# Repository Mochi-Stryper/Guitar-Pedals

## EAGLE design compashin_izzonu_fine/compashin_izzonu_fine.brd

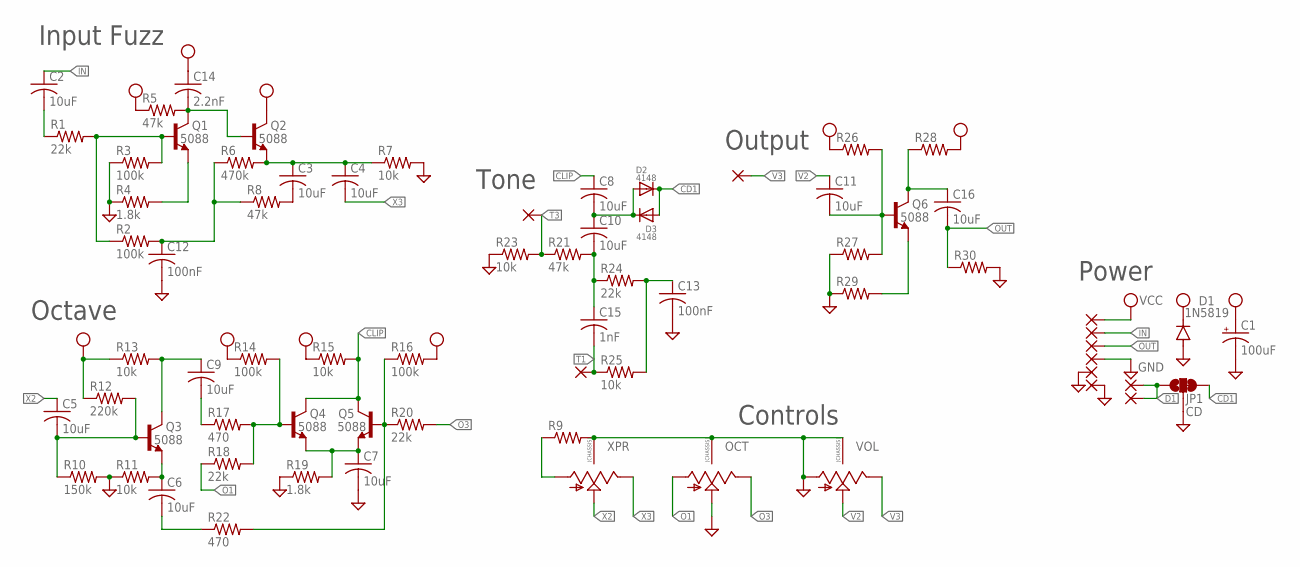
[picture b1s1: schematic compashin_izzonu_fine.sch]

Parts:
C1: 100uF; CPOL-RADIAL-2.5MM-6.5MM
C2, C3, C4, C5, C6, C7, C8, C9, C10, C11, C16: 10uF; C0805
C12, C13: 100nF; C0402
C14: 2.2nF; C0402
C15: 1nF; C0402
D1: 1N5819; SOD123
D2, D3: 4148; SOD-123
JP1: CD; SMT-JUMPER_3_1-NC_TRACE_SILK
OCT: 9MM_SNAP-IN_POT_CHASSIS; 9MM_SNAP-IN_POT
PAD1, PAD2, PAD3, PAD4, PAD5, PAD6, PAD7, PAD8: 1,6/0,8
Q1, Q2, Q3, Q4, Q5, Q6: 5088; SOT23-BEC
R1, R18, R20, R24: 22k; R0402
R2, R3, R14, R16: 100k; R0402
R4, R19: 1.8k; R0402
R5, R8, R21: 47k; R0402
R6: 470k; R0402
R7, R11, R13, R15, R23, R25: 10k; R0402
R9, R26, R27, R28, R29, R30: R-US_R0402; R0402
R10: 150k; R0402
R12: 220k; R0402
R17, R22: 470; R0402
T1, T2, T3: 1,6/0,8
VOL: 9MM_SNAP-IN_POT_CHASSIS; 9MM_SNAP-IN_POT
XPR: 9MM_SNAP-IN_POT_CHASSIS; 9MM_SNAP-IN_POT

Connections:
CD1: D2.C, D3.A, JP1.3
CLIP: C8.1, Q4.C, Q5.C, R15.2
D1: JP1.1, PAD7.1, PAD8.1
GND: C1.2 (-), C7.2, C12.2, C13.2, D1.A, JP1.2, OCT.2 (S), OCT.CHASSIS1, OCT.CHASSIS2, PAD4.1, PAD5.1, PAD6.1, R3.1, R4.1, R7.2, R9.2, R10.2, R11.1, R19.1, R23.1, R27.1, R29.1, R30.2, VOL.1 (A), VOL.CHASSIS1, VOL.CHASSIS2, XPR.CHASSIS1, XPR.CHASSIS2
IN: C2.1, PAD2.1
unnamed: Q1.B, R1.2, R2.1, R3.2
unnamed: C2.2, R1.1
unnamed: C14.2, Q1.C, Q2.B, R5.2
unnamed: Q1.E, R4.2
unnamed: C12.1, R2.2, R6.1, R8.1
unnamed: C3.1, C4.1, Q2.E, R6.2, R7.1
unnamed: C3.2, R8.2
unnamed: C5.2, Q3.B, R10.1, R12.2
unnamed: C9.1, Q3.C, R13.2
unnamed: R9.1, XPR.1 (A)
unnamed: C6.1, Q3.E, R11.2
unnamed: C9.2, R17.1
unnamed: Q4.B, R14.2, R17.2, R18.2
unnamed: C8.2, C10.1, D2.A, D3.C
unnamed: C7.1, Q4.E, Q5.E, R19.2
unnamed: Q5.B, R16.1, R20.1, R22.2
unnamed: C6.2, R22.1
unnamed: C10.2, C15.1, R21.2, R24.1
unnamed: C16.1, Q6.C, R28.1
unnamed: C13.1, R24.2, R25.2
unnamed: C11.2, Q6.B, R26.2, R27.2
unnamed: Q6.E, R29.2
O1: OCT.1 (A), R18.1
O3: OCT.3 (E), R20.2
OUT: C16.2, PAD3.1, R30.1
T1: C15.2, R25.1, T1.1
T3: R21.1, R23.2, T3.1
V2: C11.1, VOL.2 (S)
V3: T2.1, VOL.3 (E)
VCC: C1.1 (+), C14.1, D1.C, PAD1.1, Q2.C, R5.1, R12.1, R13.1, R14.1, R15.1, R16.2, R26.1, R28.2
X2: C5.1, XPR.2 (S)
X3: C4.2, XPR.3 (E)

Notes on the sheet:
Input Fuzz
Octave
Tone
Output
Power
Controls

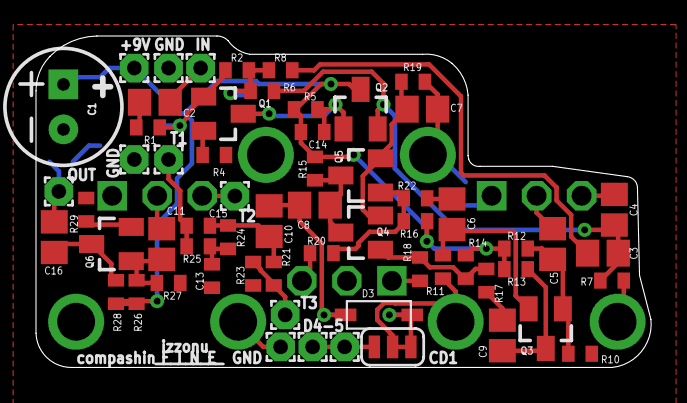
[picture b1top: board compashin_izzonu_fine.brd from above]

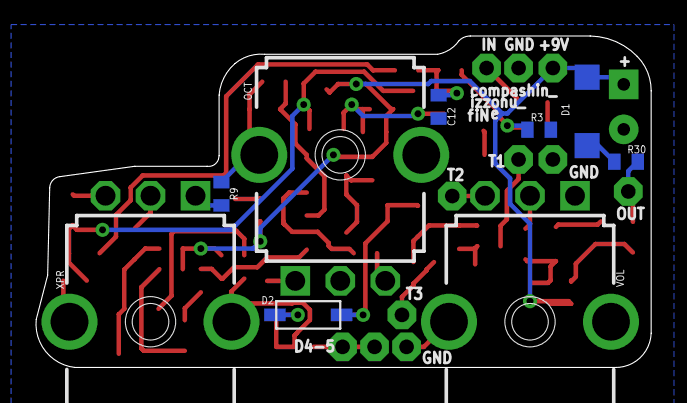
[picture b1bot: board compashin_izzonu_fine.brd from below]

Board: 2 copper layers, 34.2 x 18.4 mm, 70 parts (9 on the bottom side), 37 nets.

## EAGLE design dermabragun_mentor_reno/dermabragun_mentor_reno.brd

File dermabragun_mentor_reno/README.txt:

Mid-Fi Electronics
Random Number Generator

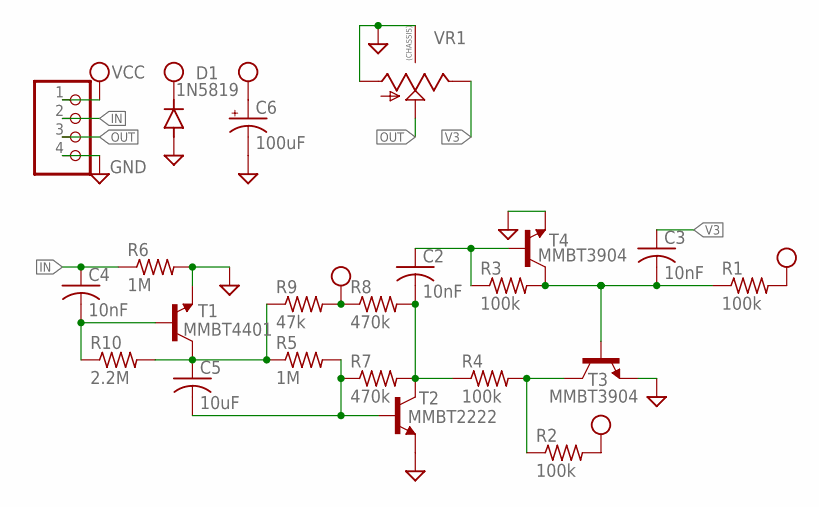
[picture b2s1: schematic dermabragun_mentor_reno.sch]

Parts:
C2, C3, C4: 10nF; C0603
C5: 10uF; CAPC3216X135
C6: 100uF; CPOL-RADIAL-2.5MM-6.5MM
D1: 1N5819; SOD123
JP1: PINHD-1X4; 1X04
R1, R2, R3, R4: 100k; R0603
R5, R6: 1M; R0603
R7, R8: 470k; R0603
R9: 47k; R0603
R10: 2.2M; R0603
T1: MMBT4401; SOT23-BEC
T2: MMBT2222; SOT23-BEC
T3, T4: MMBT3904; SOT23-BEC
VR1: 9MM_SNAP-IN_POT_CHASSIS; 9MM_SNAP-IN_POT

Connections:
GND: C6.2 (-), D1.A, JP1.4, R6.2, T1.E, T2.E, T3.E, T4.E, VR1.1 (A), VR1.CHASSIS1, VR1.CHASSIS2
IN: C4.1, JP1.2, R6.1
unnamed: C4.2, R10.1, T1.B
unnamed: C5.1, R5.1, R9.1, R10.2, T1.C
unnamed: C5.2, R5.2, R7.1, T2.B
unnamed: C2.2, R4.1, R7.2, R8.2, T2.C
unnamed: C3.2, R1.1, R3.2, T3.B, T4.C
unnamed: C2.1, R3.1, T4.B
unnamed: R2.1, R4.2, T3.C
OUT: JP1.3, VR1.2 (S)
V3: C3.1, VR1.3 (E)
VCC: C6.1 (+), D1.C, JP1.1, R1.2, R2.2, R8.1, R9.2

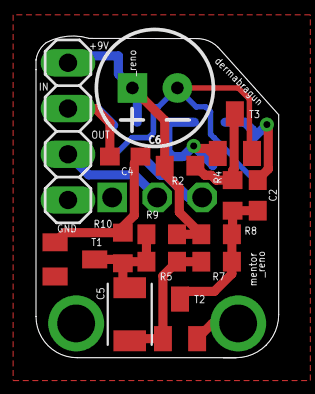
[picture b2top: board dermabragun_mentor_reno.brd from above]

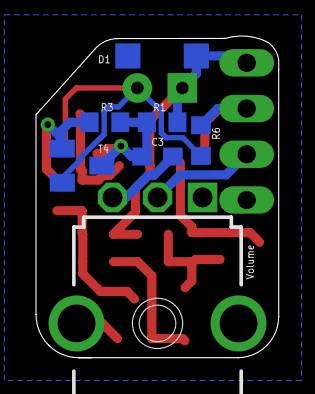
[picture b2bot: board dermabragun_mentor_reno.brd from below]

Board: 2 copper layers, 13.5 x 17.9 mm, 22 parts (7 on the bottom side), 12 nets.

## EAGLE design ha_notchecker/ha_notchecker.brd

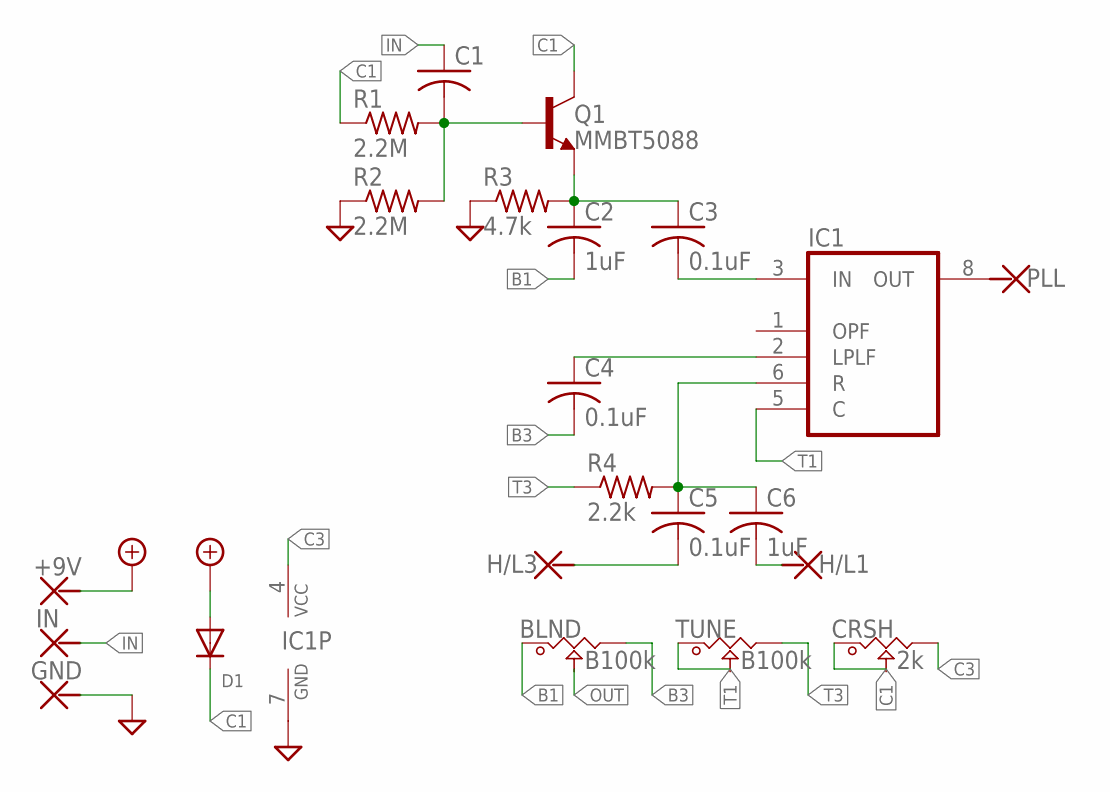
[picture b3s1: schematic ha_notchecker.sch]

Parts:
+9V: PAD
BLND: B100k; POT_9MM_SMD
C1: C-USC0603; C0603
C2, C6: 1uF; C0603
C3, C4, C5: 0.1uF; C0603
CRSH: 2k; POT_9MM_SMD
D1: DIODESOD-123; SOD-123
GND: PAD
H/L1, H/L3: PAD
IC1: XR-567K; JSOP-08
IN: PAD
PLL: PAD
Q1: MMBT5088; SOT23-BEC
R1, R2: 2.2M; R0603
R3: 4.7k; R0603
R4: 2.2k; R0603
TUNE: B100k; POT_9MM_SMD

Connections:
+9V: +9V.P$1, D1.A
B1: BLND.1, C2.2
B3: BLND.3, C4.2
C1: CRSH.1, CRSH.2, D1.C, Q1.C, R1.1
C3: CRSH.3, IC1.4 (VCC)
GND: GND.P$1, IC1.7 (GND), R2.1, R3.1
IN: C1.1, IN.P$1
unnamed: C1.2, Q1.B, R1.2, R2.2
unnamed: C2.1, C3.1, Q1.E, R3.2
unnamed: C3.2, IC1.3 (IN)
unnamed: C4.1, IC1.2 (LPLF)
unnamed: C5.1, C6.1, IC1.6 (R), R4.2
unnamed: C5.2, H/L3.P$1
unnamed: C6.2, H/L1.P$1
unnamed: IC1.8 (OUT), PLL.P$1
OUT: BLND.2
T1: IC1.5 (C), TUNE.1, TUNE.2
T3: R4.1, TUNE.3

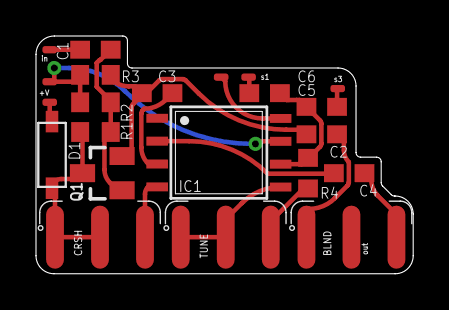
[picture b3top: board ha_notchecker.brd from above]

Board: 2 copper layers, 21.0 x 13.2 mm, 22 parts (0 on the bottom side), 17 nets.

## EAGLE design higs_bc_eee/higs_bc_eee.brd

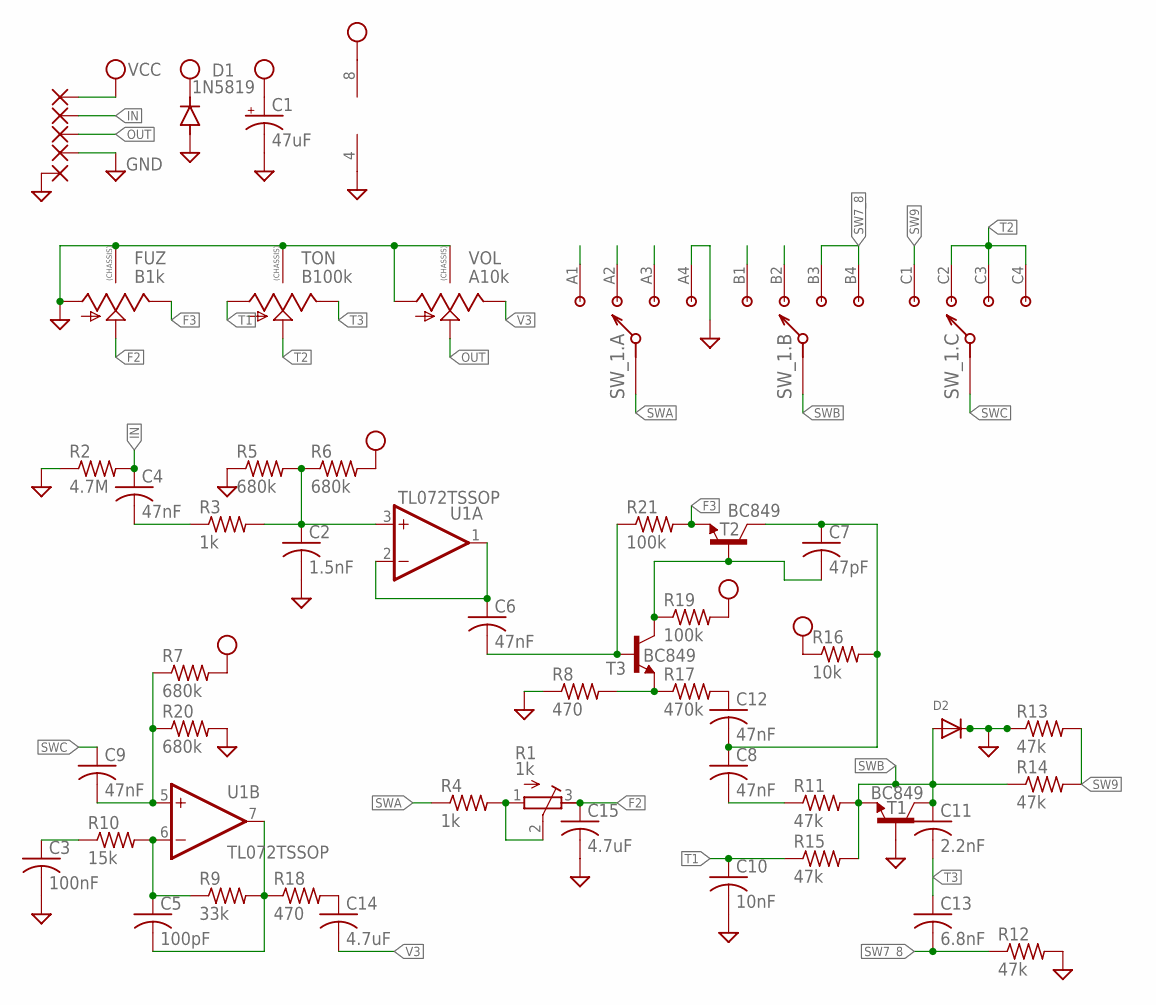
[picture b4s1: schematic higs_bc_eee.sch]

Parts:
C1: 47uF; CPOL-RADIAL-2.5MM-6.5MM
C2: 1.5nF; C0603
C3: 100nF; C0603
C4, C6, C8, C9, C12: 47nF; C0603
C5: 100pF; C0603
C7: 47pF; C0603
C10: 10nF; C0603
C11: 2.2nF; C0603
C13: 6.8nF; C0603
C14, C15: 4.7uF; C1206
D1: 1N5819; SOD123
D2: DIODESOD-123; SOD-123
FUZ: B1k; 9MM_SNAP-IN_POT
PAD1, PAD2, PAD3, PAD4, PAD5: 1,6/0,8
R1: 1k; RTRIM3224W
R2: 4.7M; R0603
R3, R4: 1k; R0603
R5, R6, R7, R20: 680k; R0603
R8, R18: 470; R0603
R9: 33k; R0603
R10: 15k; R0603
R11, R12, R13, R14, R15: 47k; R0603
R16: 10k; R0603
R17: 470k; R0603
R19, R21: 100k; R0603
SW_1: 3P4T
T1, T2, T3: BC849; SOT23-BEC
TON: B100k; 9MM_SNAP-IN_POT
U1: TL072TSSOP; TSSOP-8
VOL: A10k; 9MM_SNAP-IN_POT

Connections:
F2: C15.1, FUZ.2 (S), R1.3 (E)
F3: FUZ.3 (E), R21.2, T2.E
GND: C1.2 (-), C2.2, C3.2, C10.2, C15.2, D1.A, D2.C, FUZ.1 (A), FUZ.CHASSIS1, FUZ.CHASSIS2, PAD4.1, PAD5.1, R2.1, R5.1, R8.1, R12.2, R13.1, R20.2, SW_1.A4 (4), T1.B, TON.CHASSIS1, TON.CHASSIS2, U1.4 (V-), VOL.1 (A), VOL.CHASSIS1, VOL.CHASSIS2
IN: C4.1, PAD2.1, R2.2
unnamed: C4.2, R3.1
unnamed: C2.1, R3.2, R5.2, R6.1, U1.3 (+IN)
unnamed: C6.1, U1.1 (OUT), U1.2 (-IN)
unnamed: C7.1, C8.1, C12.2, R16.2, T2.C
unnamed: C6.2, R21.1, T3.B
unnamed: C7.2, R19.1, T2.B, T3.C
unnamed: R8.2, R17.1, T3.E
unnamed: C12.1, R17.2
unnamed: C8.2, R11.1
unnamed: C9.2, R7.1, R20.1, U1.5 (+IN)
unnamed: R1.1 (A), R1.2 (S), R4.2
unnamed: C5.1, R9.1, R10.2, U1.6 (-IN)
unnamed: C5.2, R9.2, R18.1, U1.7 (OUT)
unnamed: C3.1, R10.1
unnamed: C14.1, R18.2
OUT: PAD3.1, VOL.2 (S)
SW7_8: C13.2, R12.1, SW_1.B3 (3), SW_1.B4 (4)
SW9: R13.2, R14.2, SW_1.C1 (1)
SWA: R4.1, SW_1.A
SWB: C11.1, D2.A, R11.2, R14.1, R15.2, SW_1.B (A), T1.C, T1.E
SWC: C9.1, SW_1.C (A)
T1: C10.1, R15.1, TON.1 (A)
T2: SW_1.C2 (2), SW_1.C3 (3), SW_1.C4 (4), TON.2 (S)
T3: C11.2, C13.1, TON.3 (E)
V3: C14.2, VOL.3 (E)
VCC: C1.1 (+), D1.C, PAD1.1, R6.2, R7.2, R16.1, R19.2, U1.8 (V+)

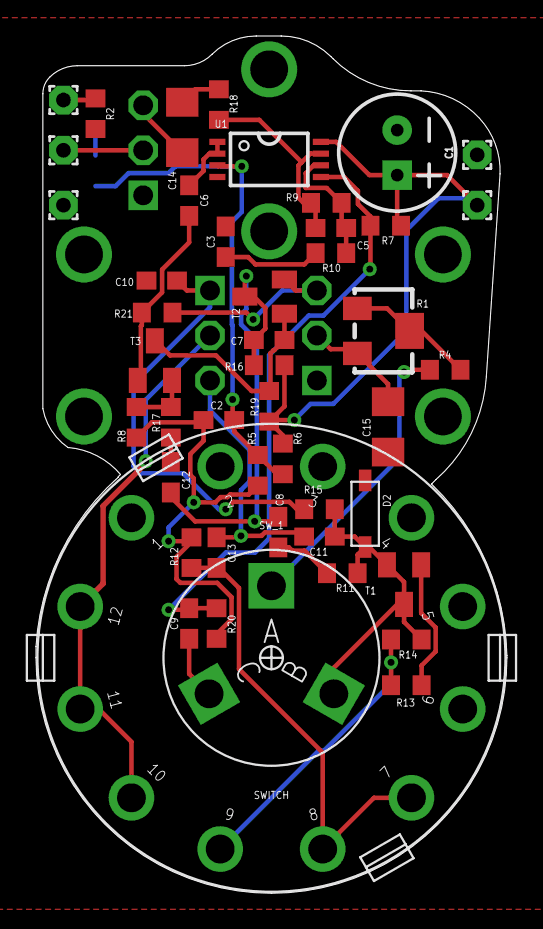
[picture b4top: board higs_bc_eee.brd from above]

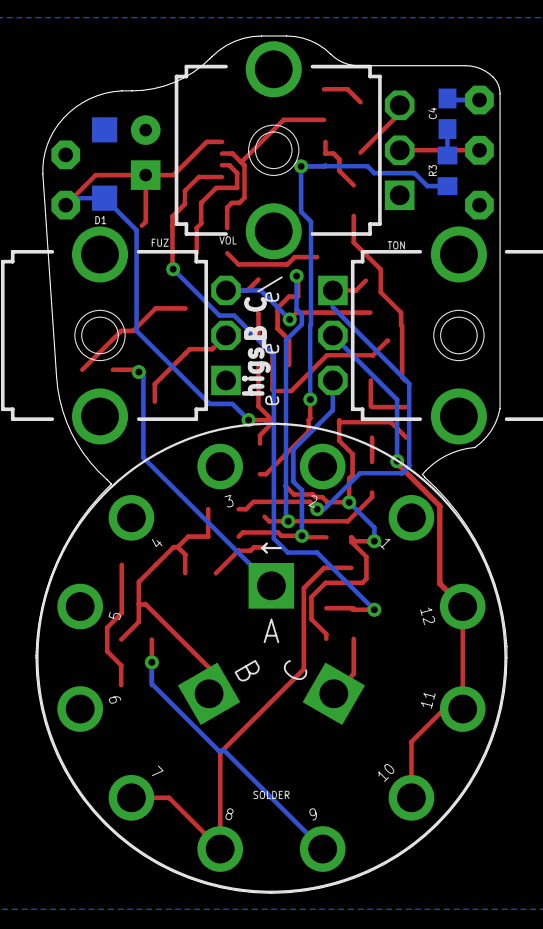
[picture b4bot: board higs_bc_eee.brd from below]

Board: 2 copper layers, 26.2 x 47.6 mm, 51 parts (7 on the bottom side), 30 nets.

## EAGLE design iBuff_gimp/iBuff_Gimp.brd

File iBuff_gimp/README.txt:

Electro Harmonix
Ram's Head Big Muff Pi
Tone Control Modification/Omission

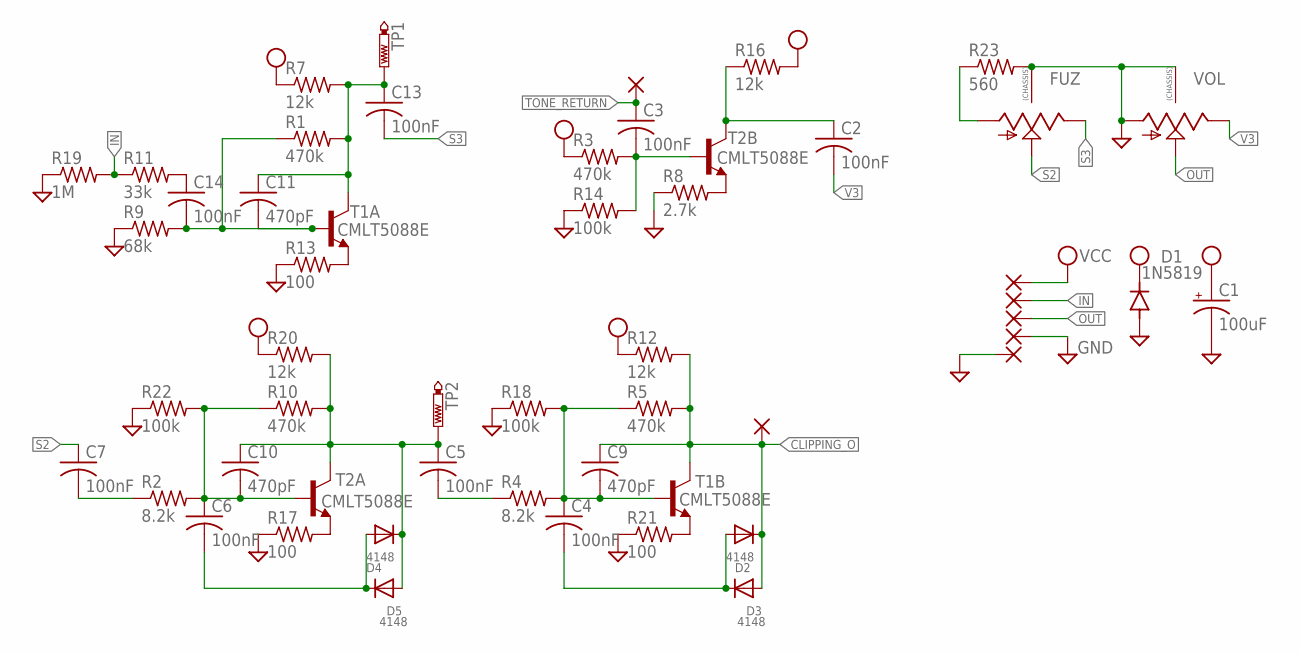
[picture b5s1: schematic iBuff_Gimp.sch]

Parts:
C1: 100uF; CPOL-RADIAL-2.5MM-6.5MM
C2, C3, C4, C5, C6, C7, C13, C14: 100nF; C0603
C9, C10, C11: 470pF; C0603
D1: 1N5819; SOD123
D2, D3, D4, D5: 4148; SOD-123
FUZ: 9MM_SNAP-IN_POT_CHASSIS; 9MM_SNAP-IN_POT
PAD1, PAD2, PAD3, PAD4, PAD5, PAD6, PAD7: 1,6/0,8
R1, R3, R5, R10: 470k; R0603
R2, R4: 8.2k; R0603
R7, R12, R16, R20: 12k; R0603
R8: 2.7k; R0603
R9: 68k; R0603
R11: 33k; R0603
R13, R17, R21: 100; R0603
R14, R18, R22: 100k; R0603
R19: 1M; R0603
R23: 560; R0603
T1, T2: CMLT5088E; SOT563
TP1, TP2: PTR1TP08R; TP08R
VOL: 9MM_SNAP-IN_POT_CHASSIS; 9MM_SNAP-IN_POT

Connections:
CLIPPING_O: C9.1, D2.C, D3.A, PAD5.1, R5.2, R12.2, T1.3 (C)
GND: C1.2 (-), D1.A, FUZ.CHASSIS1, FUZ.CHASSIS2, PAD4.1, PAD7.1, R8.1, R9.1, R13.1, R14.1, R17.1, R18.1, R19.1, R21.1, R22.1, R23.2, VOL.1 (A), VOL.CHASSIS1, VOL.CHASSIS2
IN: PAD2.1, R11.1, R19.2
unnamed: FUZ.1 (A), R23.1
unnamed: C11.2, C14.2, R1.1, R9.2, T1.2 (B)
unnamed: C14.1, R11.2
unnamed: R13.2, T1.1 (E)
unnamed: C11.1, C13.1, R1.2, R7.2, T1.6 (C), TP1.TP
unnamed: C7.2, R2.1
unnamed: C6.1, C10.2, R2.2, R10.1, R22.2, T2.2 (B)
unnamed: C5.1, C10.1, D4.C, D5.A, R10.2, R20.2, T2.6 (C), TP2.TP
unnamed: R17.2, T2.1 (E)
unnamed: C6.2, D4.A, D5.C
unnamed: C5.2, R4.1
unnamed: R21.2, T1.4 (E)
unnamed: C4.1, C9.2, R4.2, R5.1, R18.2, T1.5 (B)
unnamed: C3.2, R3.2, R14.2, T2.5 (B)
unnamed: C4.2, D2.A, D3.C
unnamed: R8.2, T2.4 (E)
unnamed: C2.1, R16.1, T2.3 (C)
OUT: PAD3.1, VOL.2 (S)
S2: C7.1, FUZ.2 (S)
S3: C13.2, FUZ.3 (E)
TONE_RETURN: C3.1, PAD6.1
V3: C2.2, VOL.3 (E)
VCC: C1.1 (+), D1.C, PAD1.1, R3.1, R7.1, R12.1, R16.2, R20.1

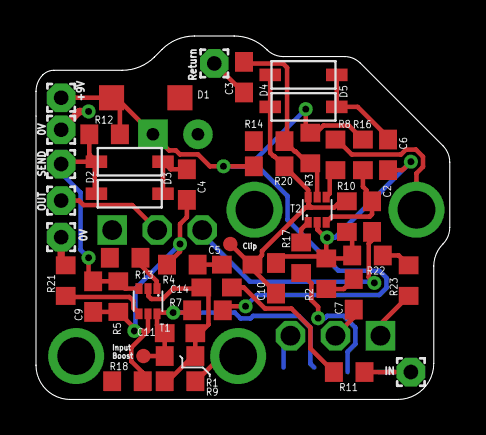
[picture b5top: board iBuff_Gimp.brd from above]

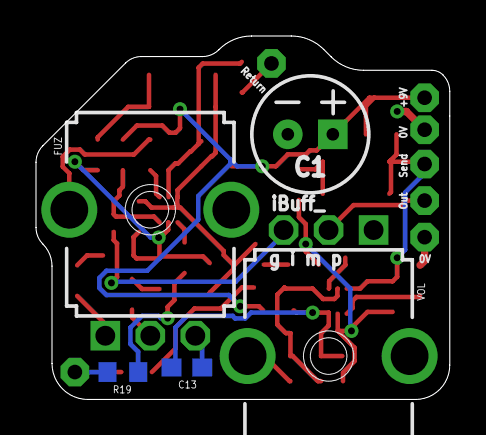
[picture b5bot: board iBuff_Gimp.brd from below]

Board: 2 copper layers, 23.0 x 20.2 mm, 51 parts (5 on the bottom side), 26 nets.

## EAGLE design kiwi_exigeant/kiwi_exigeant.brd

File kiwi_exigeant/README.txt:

Way Huge
Swollen Pickle Fuzz

BMP with Way Huge's Mods

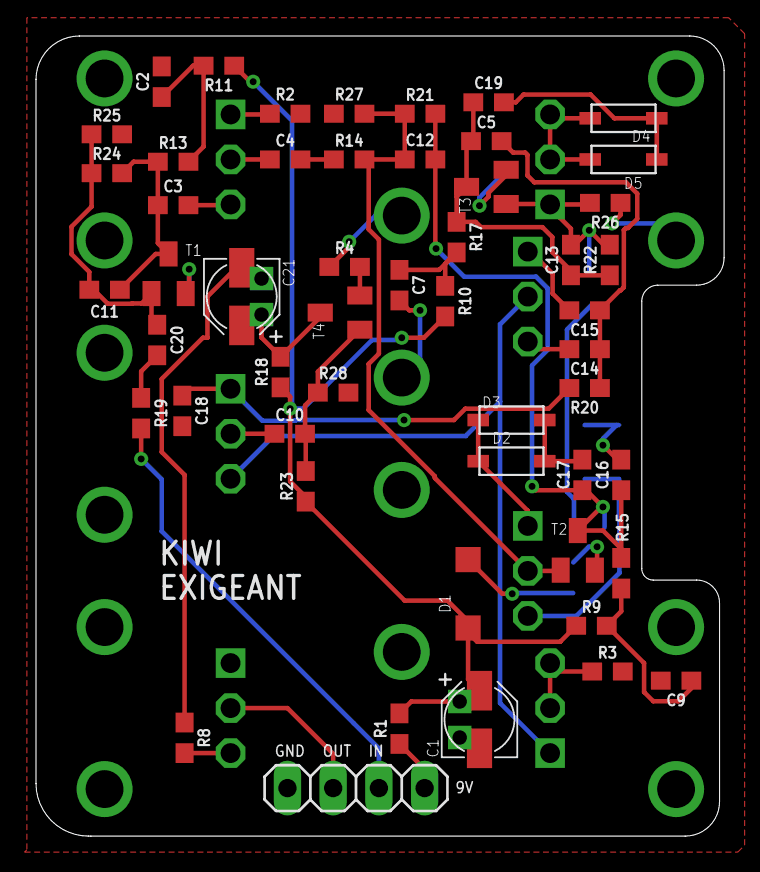
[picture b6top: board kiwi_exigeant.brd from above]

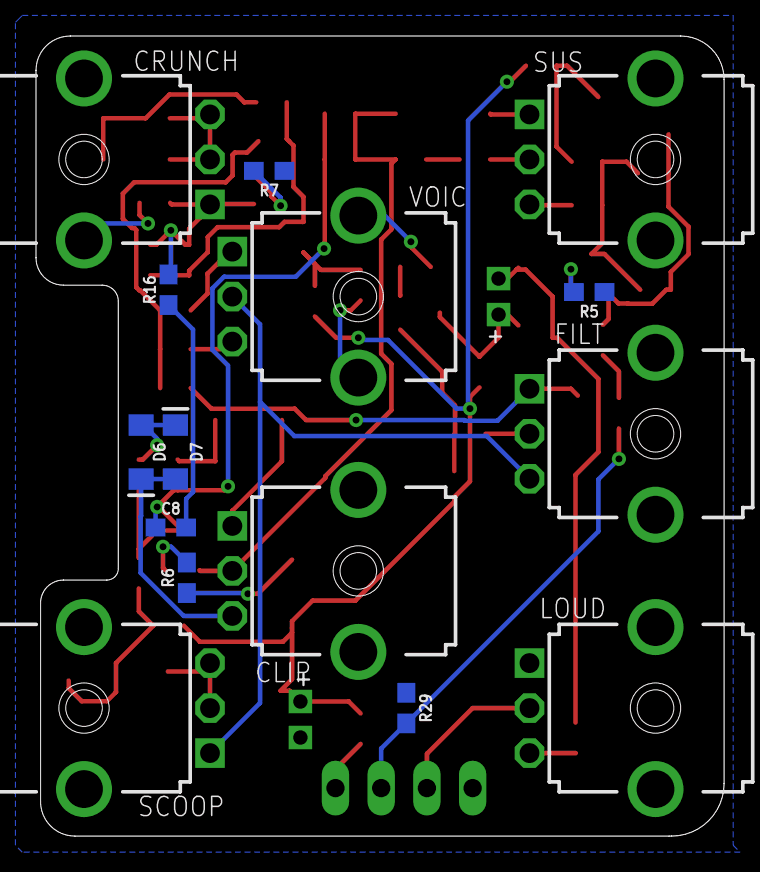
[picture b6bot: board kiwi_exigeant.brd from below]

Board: 2 copper layers, 38.2 x 44.5 mm, 67 parts (15 on the bottom side), 41 nets.

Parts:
C1: 100uF; PAN_B_SMD+THRU
C2, C3, C4, C5, C7, C8, C9, C10: 1.0uF; 0603
C11, C12, C13: 470pF; 0603
C14: 33nF; 0603
C15: 3.3nF; 0603
C16: 47nF; 0603
C17, C18, C19, C20: 0.1uF; 0603
C21: 47uF; PAN_B_SMD+THRU
CLIP: B500K; 9MM_SNAP-IN_POT
CRUNCH: A500K; 9MM_SNAP-IN_POT
D1: 1N5819; SOD123
D2, D3, D4, D5: SOD-123
D6, D7: LED-1206
FILT: B100K; 9MM_SNAP-IN_POT
JP1: PINHD-1X4; 1X04
LOUD: B100K; 9MM_SNAP-IN_POT
R1: 10; 0603
R2: 1k; 0603
R3, R4: 1.5k; 0603
R5, R6, R7: 100; 0603
R8: 150; 0603
R9, R10, R11: 4.7k; 0603
R13, R14, R15, R16, R17, R18: 10k; 0603
R19, R20: 33k; 0603
R21, R22, R23, R24: 470k; 0603
R25, R26, R27, R28: 100k; 0603
R29: 1M; 0603
SCOOP: B50K; 9MM_SNAP-IN_POT
SUS: B100K; 9MM_SNAP-IN_POT
T1, T2, T3, T4: 3904; SOT23-BEC
VOIC: B500K; 9MM_SNAP-IN_POT

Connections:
CLIP1: CLIP.1, D2.C, D3.A
CLIP2: C12.2, CLIP.2, R14.2, R21.1, R27.1, T2.B
CLIP3: CLIP.3, D6.C, D7.A
CRU1: C13.2, CRUNCH.1, R16.2, R22.1, R26.2, T3.B
CRU2: CRUNCH.2, CRUNCH.3, D4.C, D5.A
FIL1: C18.1, FILT.1, R20.2
FIL2: C10.1, FILT.2
GND: C1.-, C1.--, C2.2, C7.2, C9.2, C18.2, CLIP.CHASSIS1, CLIP.CHASSIS2, CRUNCH.CHASSIS1, CRUNCH.CHASSIS2, D1.A, FILT.CHASSIS1, FILT.CHASSIS2, JP1.4, LOUD.1, LOUD.CHASSIS1, LOUD.CHASSIS2, R2.1, R3.2, R4.1, R5.1, R6.1, R7.1, R25.2, R26.1, R27.2, R28.1, R29.1, SCOOP.CHASSIS1, SCOOP.CHASSIS2, SUS.CHASSIS1, SUS.CHASSIS2, VOIC.CHASSIS1, VOIC.CHASSIS2
IN: JP1.2, R19.1, R29.2
LOU3: LOUD.3, R8.2
unnamed: C2.1, R11.2, R13.2
unnamed: C4.2, R14.1
unnamed: C16.2, D6.A, D7.C
unnamed: C17.2, D2.A, D3.C
unnamed: C8.2, R16.1
unnamed: C7.1, R10.2, R17.2
unnamed: C19.1, D4.A, D5.C
unnamed: C5.2, C14.1, C15.1, R20.1
unnamed: C10.2, R23.2, R28.2, T4.B
unnamed: R4.2, T4.E
unnamed: C21.+, C21.++, R18.2, T4.C
unnamed: C21.-, C21.--, R8.1
unnamed: C8.1, C12.1, C16.1, C17.1, R15.1, R21.2, T2.C
unnamed: R6.2, T2.E
unnamed: C20.1, R19.2
unnamed: JP1.1, R1.1
unnamed: C11.2, C20.2, R24.2, R25.1, T1.B
unnamed: R5.2, T1.E
unnamed: C3.1, C11.1, R13.1, R24.1, T1.C
unnamed: C9.1, R9.2, R15.2
unnamed: C5.1, C13.1, C19.2, R17.1, R22.2, T3.C
unnamed: R7.2, T3.E
OUT: JP1.3, LOUD.2
SCO2: R3.1, SCOOP.2, SCOOP.3
SUS1: R2.2, SUS.1
SUS2: C4.1, SUS.2
SUS3: C3.2, SUS.3
VCC: C1.+, C1.++, D1.C, R1.2, R9.1, R10.1, R11.1, R18.1, R23.1
VOI1: C15.2, VOIC.1
VOI2: FILT.3, SCOOP.1, VOIC.2
VOI3: C14.2, VOIC.3

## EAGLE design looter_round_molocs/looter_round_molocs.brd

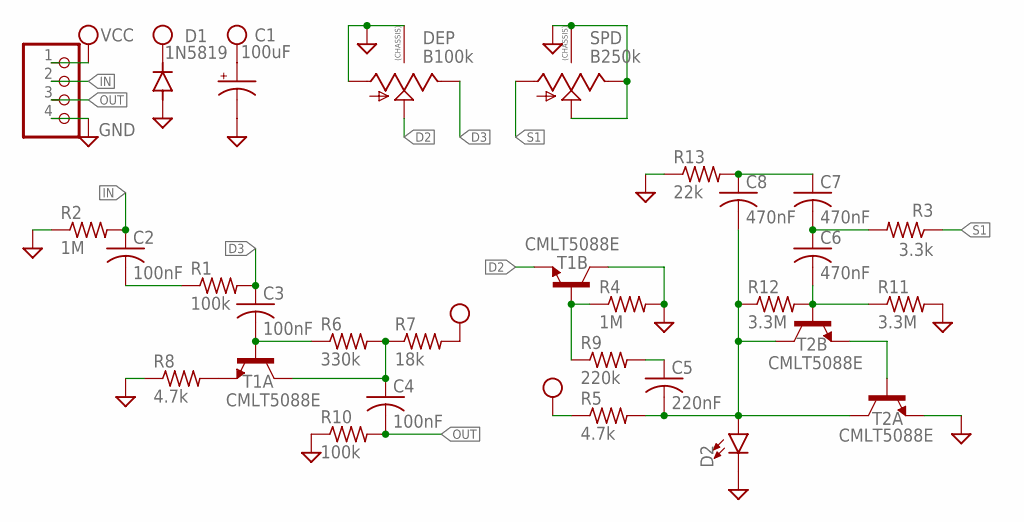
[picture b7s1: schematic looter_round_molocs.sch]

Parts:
C1: 100uF; PAN_B_SMD+THRU
C2, C3, C4: 100nF; C0603
C5: 220nF; C0603
C6, C7, C8: 470nF; C0603
D1: 1N5819; SOD123
D2: LED0603; LED-0603
DEP: B100k; 9MM_SNAP-IN_POT
JP1: PINHD-1X4; 1X04
R1, R10: 100k; R0603
R2, R4: 1M; R0603
R3: 3.3k; R0603
R5, R8: 4.7k; R0603
R6: 330k; R0603
R7: 18k; R0603
R9: 220k; R0603
R11, R12: 3.3M; R0603
R13: 22k; R0603
SPD: B250k; 9MM_SNAP-IN_POT
T1, T2: CMLT5088E; SOT563

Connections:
D2: DEP.2 (S), T1.4 (E)
D3: C3.1, DEP.3 (E), R1.2
GND: C1.-, C1.-- (-), D1.A, D2.C, DEP.1 (A), DEP.CHASSIS1, DEP.CHASSIS2, JP1.4, R2.1, R4.2, R8.1, R10.1, R11.2, R13.1, SPD.2 (S), SPD.3 (E), SPD.CHASSIS1, SPD.CHASSIS2, T1.3 (C), T2.1 (E)
IN: C2.1, JP1.2, R2.2
unnamed: C2.2, R1.1
unnamed: C3.2, R6.1, T1.2 (B)
unnamed: R8.2, T1.1 (E)
unnamed: C4.1, R6.2, R7.1, T1.6 (C)
unnamed: R4.1, R9.1, T1.5 (B)
unnamed: C5.1, R9.2
unnamed: C5.2, C8.2, D2.A, R5.2, R12.1, T2.3 (C), T2.6 (C)
unnamed: T2.2 (B), T2.4 (E)
unnamed: C6.2, R11.1, R12.2, T2.5 (B)
unnamed: C6.1, C7.2, R3.2
unnamed: C7.1, C8.1, R13.2
OUT: C4.2, JP1.3, R10.2
S1: R3.1, SPD.1 (A)
VCC: C1.+, C1.++ (+), D1.C, JP1.1, R5.1, R7.2

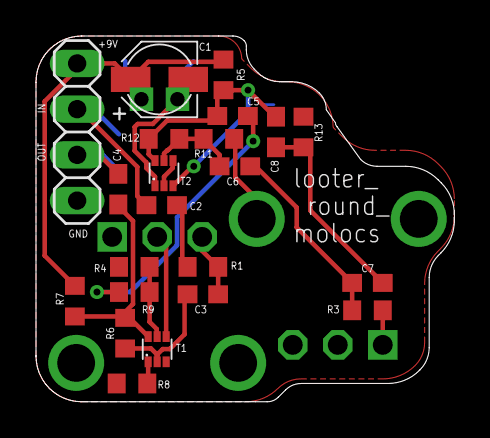
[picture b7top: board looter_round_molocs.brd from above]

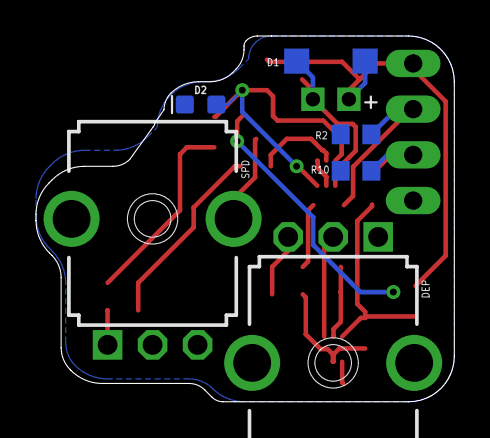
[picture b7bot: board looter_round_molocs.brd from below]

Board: 2 copper layers, 23.2 x 20.3 mm, 28 parts (6 on the bottom side), 18 nets.

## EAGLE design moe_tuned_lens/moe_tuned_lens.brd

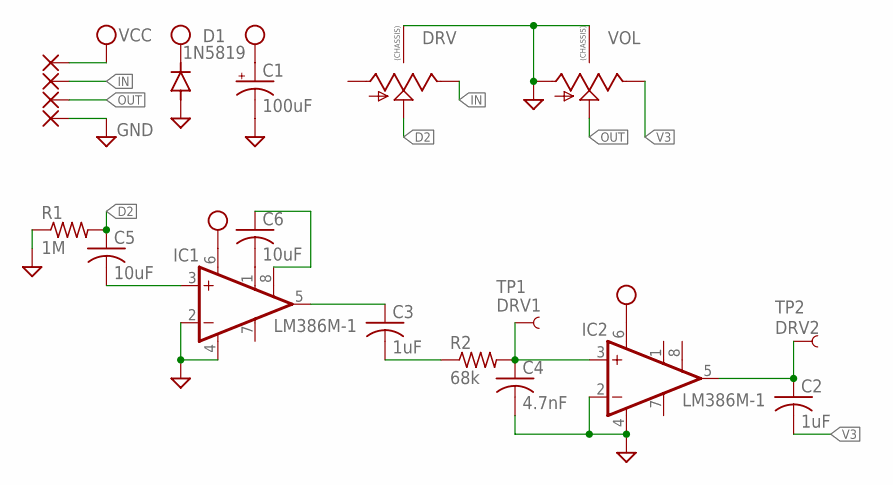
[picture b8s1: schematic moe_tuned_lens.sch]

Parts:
C1: 100uF; CPOL-RADIAL-2.5MM-6.5MM
C2, C3: 1uF; C0805
C4: 4.7nF; C0805
C5, C6: 10uF; C1206
D1: 1N5819; SOD123
DRV: 9MM_SNAP-IN_POT_CHASSIS; 9MM_SNAP-IN_POT
IC1, IC2: LM386M-1; SO08
PAD1, PAD2, PAD3, PAD4: 1,6/0,8
R1: 1M; R0805
R2: 68k; R0805
TP1: DRV1; PAD.03X.03
TP2: DRV2; PAD.03X.03
VOL: 9MM_SNAP-IN_POT_CHASSIS; 9MM_SNAP-IN_POT

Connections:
D2: C5.1, DRV.2 (S), R1.2
GND: C1.2 (-), C4.2, D1.A, DRV.CHASSIS1, DRV.CHASSIS2, IC1.2 (-IN), IC1.4 (GND), IC2.2 (-IN), IC2.4 (GND), PAD4.1, R1.1, VOL.1 (A), VOL.CHASSIS1, VOL.CHASSIS2
IN: DRV.3 (E), PAD2.1
unnamed: C5.2, IC1.3 (+IN)
unnamed: C6.2, IC1.1 (GAIN)
unnamed: C6.1, IC1.8 (GAIN)
unnamed: C3.1, IC1.5 (OUT)
unnamed: C3.2, R2.1
unnamed: C4.1, IC2.3 (+IN), R2.2, TP1.P$1
unnamed: C2.1, IC2.5 (OUT), TP2.P$1
OUT: PAD3.1, VOL.2 (S)
V3: C2.2, VOL.3 (E)
VCC: C1.1 (+), D1.C, IC1.6 (VS), IC2.6 (VS), PAD1.1

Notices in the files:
parts and their libraries:
SparkFun-Capacitors: Licensing: Creative Commons ShareAlike 4.0 International - https://creativecommons.org/licenses/by-sa/4.0
